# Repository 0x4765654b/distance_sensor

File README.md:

# SaltMon — Water-Softener Salt Level Monitor

SaltMon watches the salt tank of a Culligan Gold Series water softener. A US-100 ultrasonic sensor, mounted under
the tank lid, measures the distance down to the salt. An ESP32-C6 in a wall-mounted box turns that distance into a
salt level. It shows the level on lid LEDs and publishes readings to AWS IoT Core. A SaltMon AWS stack stores the
history, forecasts when the salt will run out, and publishes the results over SNS. There, the ChoreCore household
app picks them up and creates an "Add salt" chore.

**Status:** design phase. The requirements, the carrier schematic and the routed carrier PCB are done. Firmware,
the cloud stack and the tooling are not started yet.

## Repository Layout

```
docs/                     requirements, pin map, integration contract, pick list, datasheets
kicad/lib/                ESP32-C6-DevKitM-1 symbol + socketed footprint (generated)
kicad/DepthSensor/        carrier PCB project (KiCad 10): schematic, board, Gerbers, generator scripts
models/                   ESP32-S3 dev-kit library (not used; kept for reference)
firmware/                 ESP-IDF application                      (planned)
cloud/                    SaltMon-<env> CDK stack + Lambdas        (planned)
tools/                    provision.py, saltmon-config.py          (planned)
```

## Documents

| Document | Contents |
|---|---|
| [docs/requirements.md](docs/requirements.md) | System requirements: design decisions, parts, power, LEDs, sensor, firmware, cloud, mechanics, verification |
| [docs/pinmap.md](docs/pinmap.md) | Kit header pads, carrier connectors, U2 pinout. Source of truth for firmware `board.h` |
| [docs/integration-contract.md](docs/integration-contract.md) | SNS message contract between SaltMon and its consumers (ChoreCore) |
| [docs/pick-list.md](docs/pick-list.md) | Everything to buy or gather for one build (carrier, cables, enclosure) |
| [docs/lid-pick-list.md](docs/lid-pick-list.md) | The lid panel board: parts, LED spacers, mounting hardware, assembly order |

## Hardware

- **Carrier PCB:** 80.5 × 92 mm, 2-layer, all through-hole. The ESP32-C6-DevKitM-1 plugs into female headers.
  The board also carries a TBD62783APG LED driver, the power path (fuse, lid switch loop, Schottky diode), the
  sensor-line filters, and keyed headers for the lid ribbon (J_PANEL) and the sensor ribbon (J_SNS).
- **Lid panel PCB:** 50 × 63 mm, passive, on standoffs behind the lid. It holds 8 flat-top LEDs (salt level,
  network, activity, power) and pads for the panel-mounted on/off slide switch and push-button. A 16-way ribbon
  with an IDC socket at each end connects it 1:1 to the carrier. The same KiCad file carries the 1:1 lid drilling
  template on User.Drawings. What each LED shows is in requirements §5.4.
- **Sensor:** a US-100 in UART mode on a 6-way ribbon, about 1.2 m long.
- **Enclosure:** a gasketed ABS junction box, wall-mounted through its 4 corner holes.

Gerbers for fabrication are in `kicad/DepthSensor/depth_gerber/` (also zipped as `depth_gerber.zip`).

### Regenerating the Schematic and PCB

The schematic, the kit footprint and the PCB are all generated by scripts. Change the script, not the KiCad file,
then regenerate:

```sh
KICAD=/Applications/KiCad/KiCad.app/Contents
KPY=$KICAD/Frameworks/Python.framework/Versions/Current/bin/python3   # KiCad's Python (has pcbnew)
CLI=$KICAD/MacOS/kicad-cli

python3 kicad/lib/gen_devkit.py                    # kit symbol + footprint
python3 kicad/DepthSensor/gen_schematic.py         # schematic (deterministic UUIDs)
$CLI sch erc kicad/DepthSensor/DepthSensor.kicad_sch

$KPY kicad/DepthSensor/gen_pcb.py                  # place, autoroute (Freerouting), pour GND
$KPY kicad/DepthSensor/gen_pcb.py --no-route       # placement only
$CLI pcb drc --schematic-parity kicad/DepthSensor/DepthSensor.kicad_pcb

python3 kicad/LidPanel/gen_schematic.py           # lid panel: same steps
$KPY kicad/LidPanel/gen_pcb.py
$CLI pcb drc --schematic-parity kicad/LidPanel/LidPanel.kicad_pcb
$CLI pcb export pdf --mode-single -l User.Drawings --scale 1 -o lid-template.pdf kicad/LidPanel/LidPanel.kicad_pcb
```

Helpers shared by both boards are in `kicad/lib/schgen.py` (schematic) and `kicad/lib/pcbgen.py` (PCB).

`gen_pcb.py` needs Java 21+ and the Freerouting jar at `kicad/freerouting/freerouting-*.jar`. The jar is not in git;
download it from the [Freerouting releases](https://github.com/freerouting/freerouting/releases). It was tested
with 2.4.1. Close the board in KiCad before regenerating, and re-export the Gerbers afterwards.

## License

[MIT](LICENSE)

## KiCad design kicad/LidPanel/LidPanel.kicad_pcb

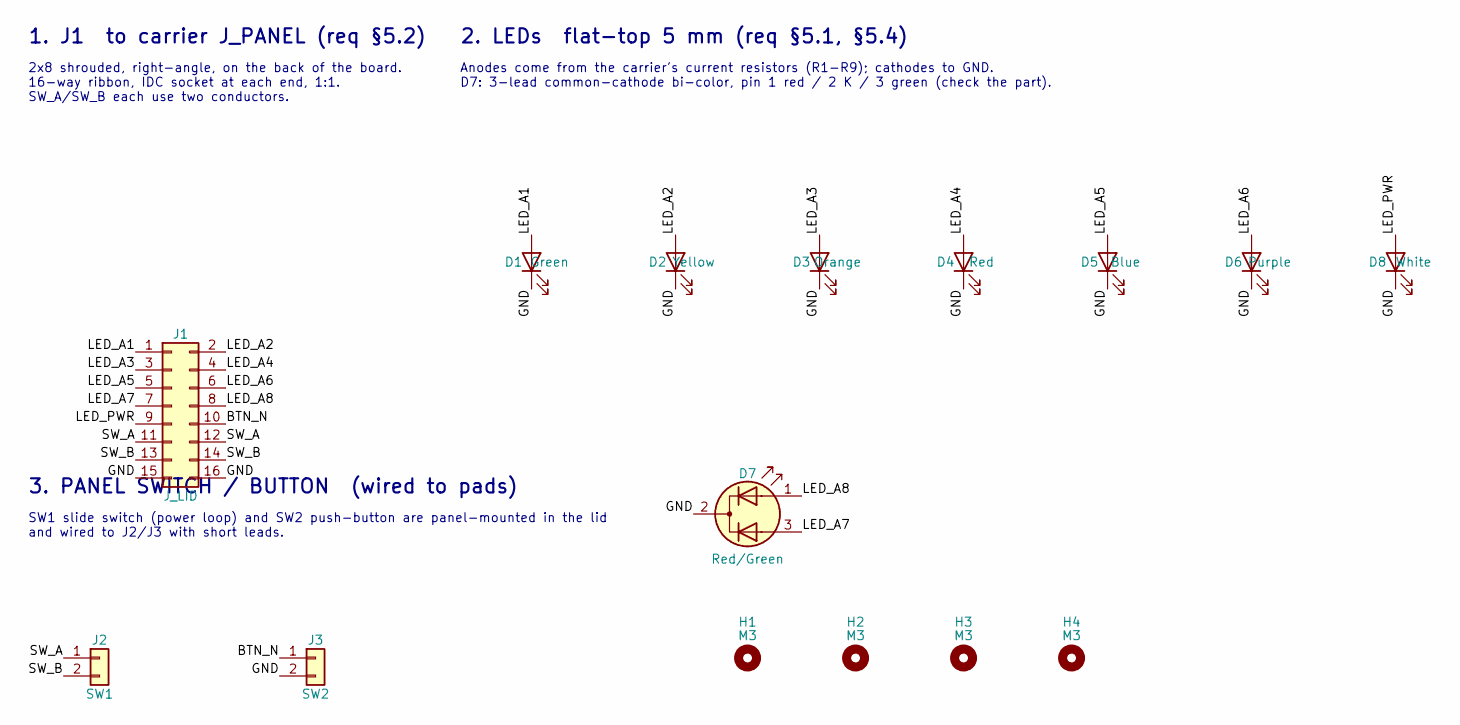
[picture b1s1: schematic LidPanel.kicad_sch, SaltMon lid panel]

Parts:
D1: Green; LED_D5.0mm_FlatTop
D2: Yellow; LED_D5.0mm_FlatTop
D3: Orange; LED_D5.0mm_FlatTop
D4: Red; LED_D5.0mm_FlatTop
D5: Blue; LED_D5.0mm_FlatTop
D6: Purple; LED_D5.0mm_FlatTop
D7: Red/Green; LED_D5.0mm-3
D8: White; LED_D5.0mm_FlatTop
H1, H2, H3, H4: M3; MountingHole_3.2mm_M3
J1: J_LID; IDC-Header_2x08_P2.54mm_Horizontal
J2: SW1; SolderWire-0.5sqmm_1x02_P4.6mm_D0.9mm_OD2.1mm
J3: SW2; SolderWire-0.5sqmm_1x02_P4.6mm_D0.9mm_OD2.1mm

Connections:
/BTN_N: J1.10, J3.1
/GND: D1.1 (K), D2.1 (K), D3.1 (K), D4.1 (K), D5.1 (K), D6.1 (K), D7.2 (K), D8.1 (K), J1.15, J1.16, J3.2
/LED_A1: D1.2 (A), J1.1
/LED_A2: D2.2 (A), J1.2
/LED_A3: D3.2 (A), J1.3
/LED_A4: D4.2 (A), J1.4
/LED_A5: D5.2 (A), J1.5
/LED_A6: D6.2 (A), J1.6
/LED_A7: D7.3 (A2), J1.7
/LED_A8: D7.1 (A1), J1.8
/LED_PWR: D8.2 (A), J1.9
/SW_A: J1.11, J1.12, J2.1
/SW_B: J1.13, J1.14, J2.2

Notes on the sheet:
1. J1 to carrier J_PANEL (req §5.2)
2x8 shrouded, right-angle, on the back of the board. 16-way ribbon, IDC socket at each end, 1:1. SW_A/SW_B each use two conductors.
2. LEDs flat-top 5 mm (req §5.1, §5.4)
Anodes come from the carrier's current resistors (R1-R9); cathodes to GND. D7: 3-lead common-cathode bi-color, pin 1 red / 2 K / 3 green (check the part).
3. PANEL SWITCH / BUTTON (wired to pads)
SW1 slide switch (power loop) and SW2 push-button are panel-mounted in the lid and wired to J2/J3 with short leads.

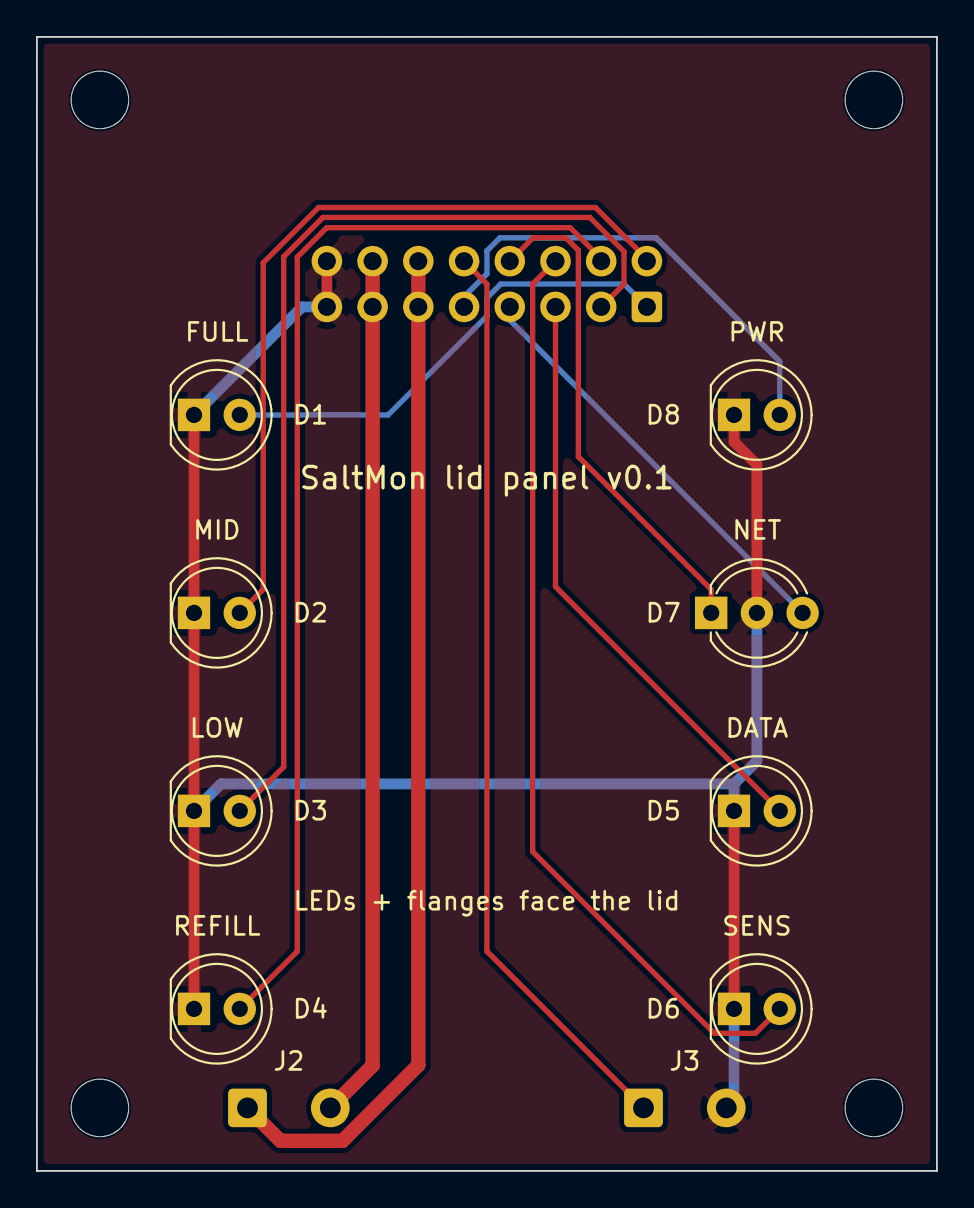
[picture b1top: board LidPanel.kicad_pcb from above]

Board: 2 copper layers, 50.0 x 63.0 mm, 15 parts (1 on the bottom side), 13 nets.

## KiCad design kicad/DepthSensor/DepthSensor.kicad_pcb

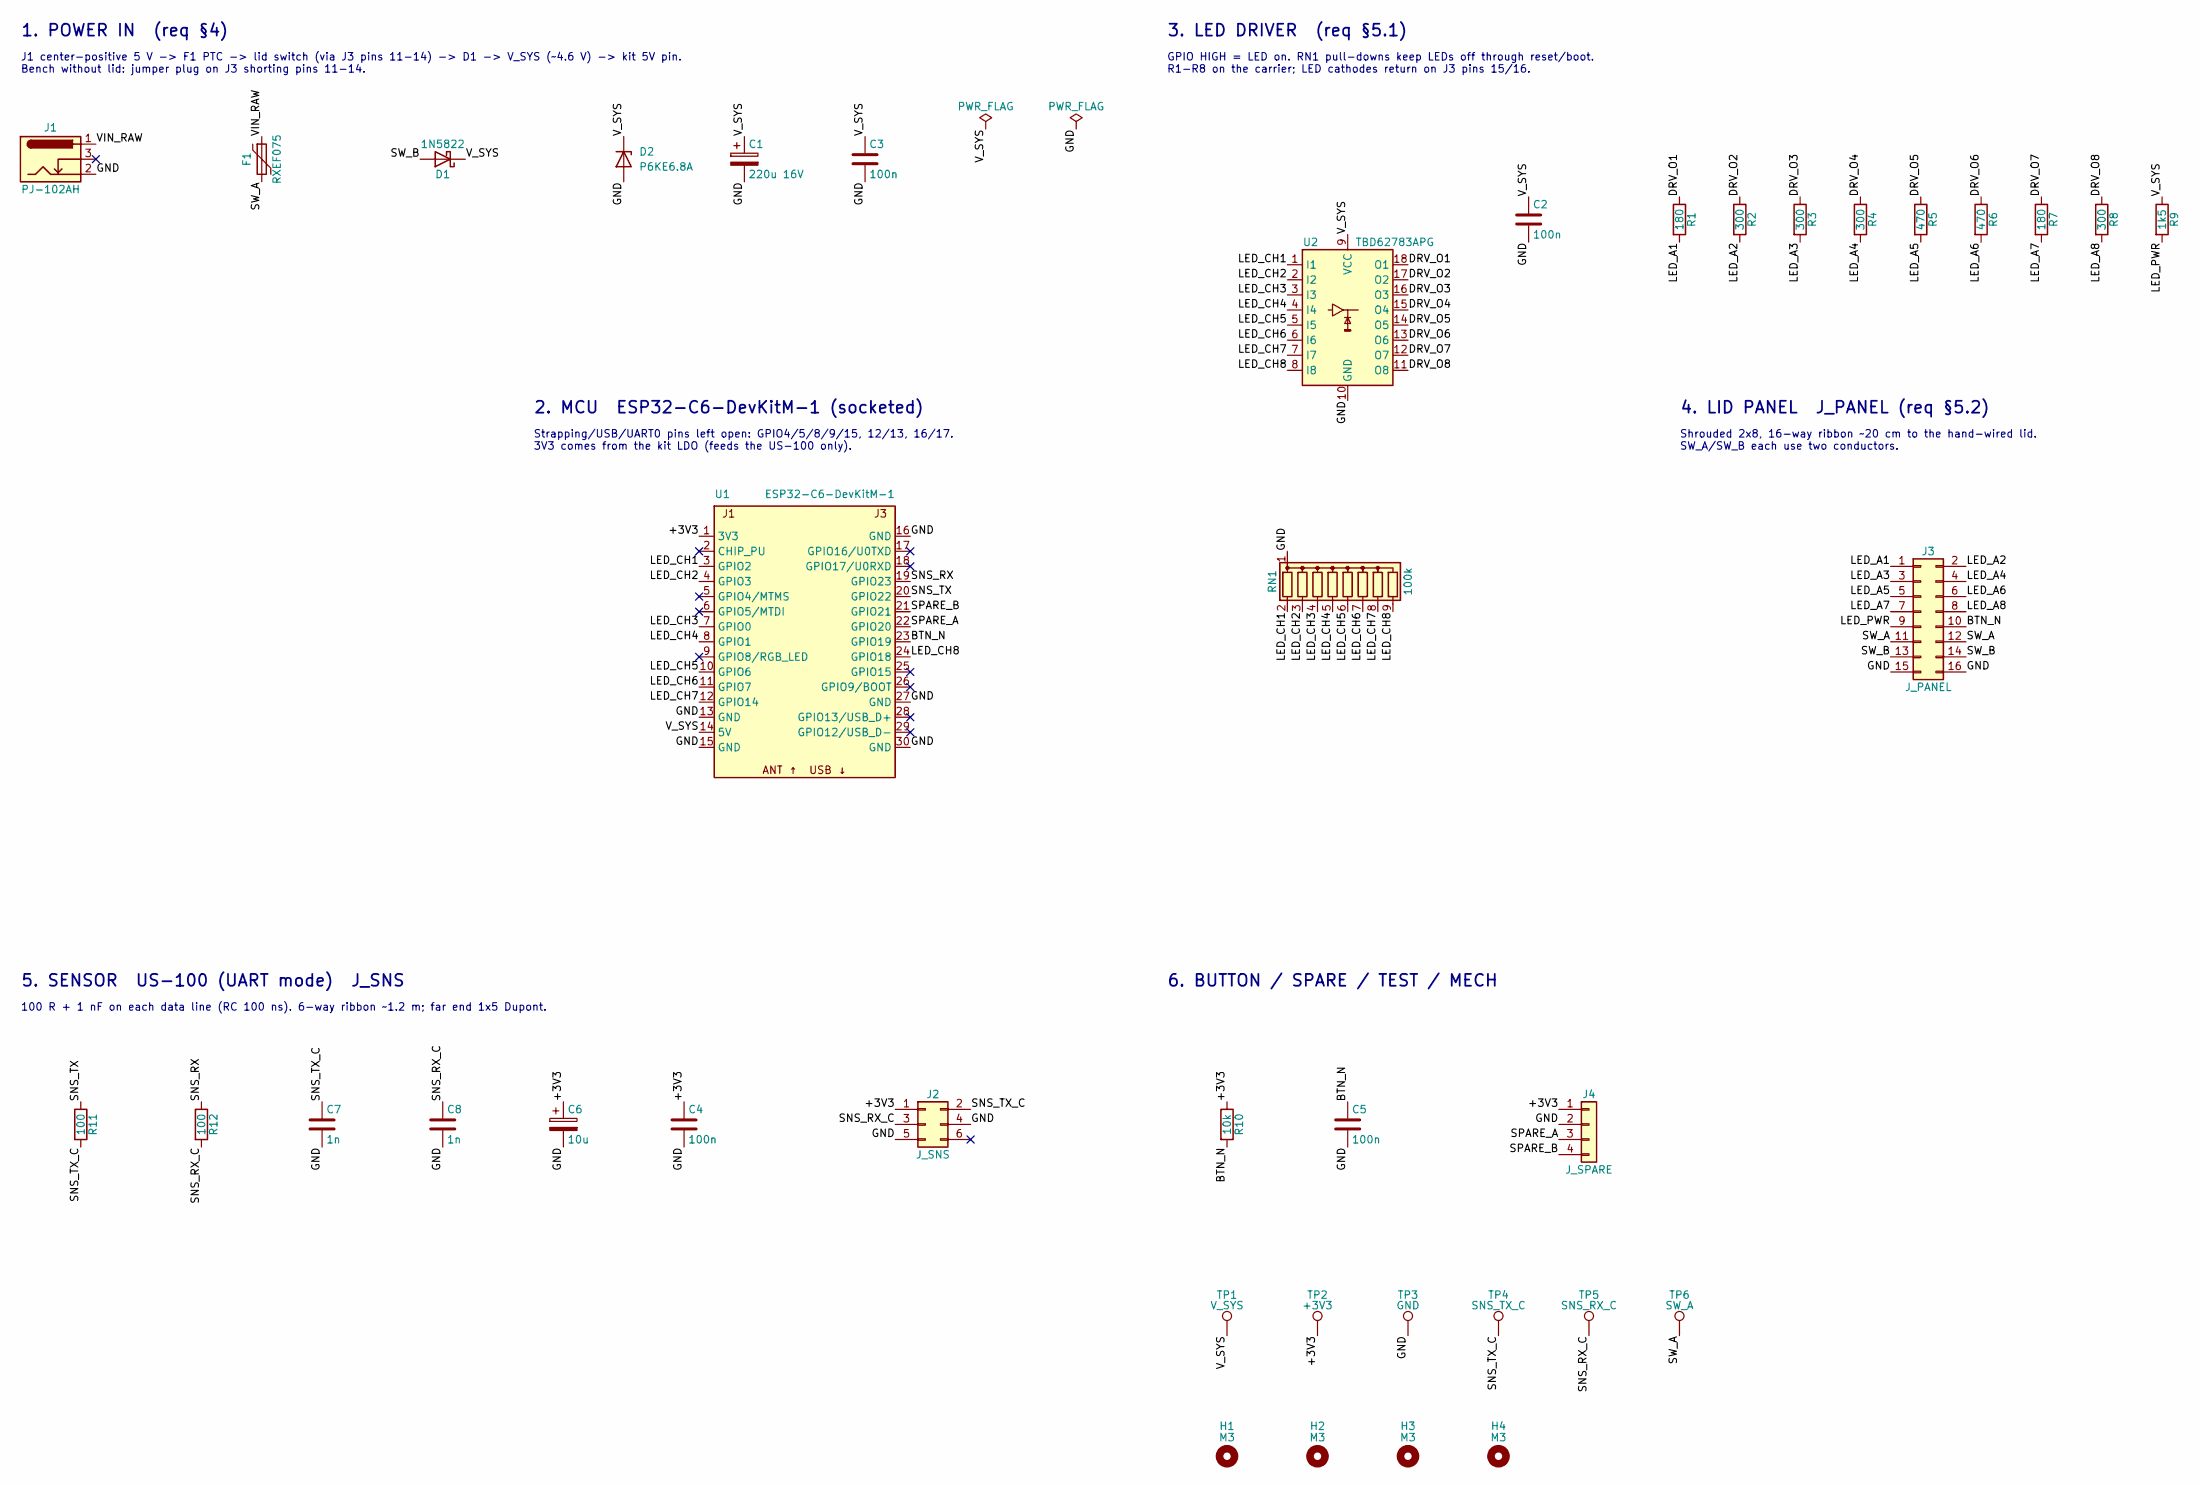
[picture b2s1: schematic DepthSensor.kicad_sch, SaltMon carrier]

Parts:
C1: 220u 16V; CP_Radial_D8.0mm_P3.50mm
C2, C3, C4, C5: 100n; C_Disc_D5.0mm_W2.5mm_P5.00mm
C6: 10u; CP_Radial_D5.0mm_P2.00mm
C7, C8: 1n; C_Disc_D5.0mm_W2.5mm_P5.00mm
D1: 1N5822; D_DO-201AD_P15.24mm_Horizontal
D2: P6KE6.8A; D_DO-15_P10.16mm_Horizontal
F1: RXEF075; Fuse_Bourns_MF-RHT070
H1, H2, H3, H4: M3; MountingHole_3.2mm_M3
J1: PJ-102AH; BarrelJack_CUI_PJ-102AH_Horizontal
J2: J_SNS; IDC-Header_2x03_P2.54mm_Vertical
J3: J_PANEL; IDC-Header_2x08_P2.54mm_Vertical
J4: J_SPARE; PinHeader_1x04_P2.54mm_Vertical
R1, R7: 180; R_Axial_DIN0207_L6.3mm_D2.5mm_P10.16mm_Horizontal
R2, R3, R4, R8: 300; R_Axial_DIN0207_L6.3mm_D2.5mm_P10.16mm_Horizontal
R5, R6: 470; R_Axial_DIN0207_L6.3mm_D2.5mm_P10.16mm_Horizontal
R9: 1k5; R_Axial_DIN0207_L6.3mm_D2.5mm_P10.16mm_Horizontal
R10: 10k; R_Axial_DIN0207_L6.3mm_D2.5mm_P10.16mm_Horizontal
R11, R12: 100; R_Axial_DIN0207_L6.3mm_D2.5mm_P10.16mm_Horizontal
RN1: 100k; R_Array_SIP9
TP1: V_SYS; TestPoint_THTPad_1.5x1.5mm_Drill0.7mm
TP2: +3V3; TestPoint_THTPad_1.5x1.5mm_Drill0.7mm
TP3: GND; TestPoint_THTPad_1.5x1.5mm_Drill0.7mm
TP4: SNS_TX_C; TestPoint_THTPad_1.5x1.5mm_Drill0.7mm
TP5: SNS_RX_C; TestPoint_THTPad_1.5x1.5mm_Drill0.7mm
TP6: SW_A; TestPoint_THTPad_1.5x1.5mm_Drill0.7mm
U1: ESP32-C6-DevKitM-1; ESP32-C6-DevKitM-1_Socketed
U2: TBD62783APG; DIP-18_W7.62mm_Socket

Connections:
/+3V3: C4.1, C6.1, J2.1, J4.1, R10.1, TP2.1, U1.1 (3V3)
/BTN_N: C5.1, J3.10, R10.2, U1.23 (GPIO19)
/DRV_O1: R1.1, U2.18 (O1)
/DRV_O2: R2.1, U2.17 (O2)
/DRV_O3: R3.1, U2.16 (O3)
/DRV_O4: R4.1, U2.15 (O4)
/DRV_O5: R5.1, U2.14 (O5)
/DRV_O6: R6.1, U2.13 (O6)
/DRV_O7: R7.1, U2.12 (O7)
/DRV_O8: R8.1, U2.11 (O8)
/GND: C1.2, C2.2, C3.2, C4.2, C5.2, C6.2, C7.2, C8.2, D2.2 (A), J1.2, J2.4, J2.5, J3.15, J3.16, J4.2, RN1.1 (common), TP3.1, U1.13 (GND), U1.15 (GND), U1.16 (GND), U1.27 (GND), U1.30 (GND), U2.10 (GND)
/LED_A1: J3.1, R1.2
/LED_A2: J3.2, R2.2
/LED_A3: J3.3, R3.2
/LED_A4: J3.4, R4.2
/LED_A5: J3.5, R5.2
/LED_A6: J3.6, R6.2
/LED_A7: J3.7, R7.2
/LED_A8: J3.8, R8.2
/LED_CH1: RN1.2 (R1), U1.3 (GPIO2), U2.1 (I1)
/LED_CH2: RN1.3 (R2), U1.4 (GPIO3), U2.2 (I2)
/LED_CH3: RN1.4 (R3), U1.7 (GPIO0), U2.3 (I3)
/LED_CH4: RN1.5 (R4), U1.8 (GPIO1), U2.4 (I4)
/LED_CH5: RN1.6 (R5), U1.10 (GPIO6), U2.5 (I5)
/LED_CH6: RN1.7 (R6), U1.11 (GPIO7), U2.6 (I6)
/LED_CH7: RN1.8 (R7), U1.12 (GPIO14), U2.7 (I7)
/LED_CH8: RN1.9 (R8), U1.24 (GPIO18), U2.8 (I8)
/LED_PWR: J3.9, R9.2
/SNS_RX: R12.1, U1.19 (GPIO23)
/SNS_RX_C: C8.1, J2.3, R12.2, TP5.1
/SNS_TX: R11.1, U1.20 (GPIO22)
/SNS_TX_C: C7.1, J2.2, R11.2, TP4.1
/SPARE_A: J4.3, U1.22 (GPIO20)
/SPARE_B: J4.4, U1.21 (GPIO21)
/SW_A: F1.2, J3.11, J3.12, TP6.1
/SW_B: D1.2 (A), J3.13, J3.14
/VIN_RAW: F1.1, J1.1
/V_SYS: C1.1, C2.1, C3.1, D1.1 (K), D2.1 (K), R9.1, TP1.1, U1.14 (5V), U2.9 (VCC)

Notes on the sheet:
1. POWER IN (req §4)
J1 center-positive 5 V -> F1 PTC -> lid switch (via J3 pins 11-14) -> D1 -> V_SYS (~4.6 V) -> kit 5V pin. Bench without lid: jumper plug on J3 shorting pins 11-14.
2. MCU ESP32-C6-DevKitM-1 (socketed)
Strapping/USB/UART0 pins left open: GPIO4/5/8/9/15, 12/13, 16/17. 3V3 comes from the kit LDO (feeds the US-100 only).
3. LED DRIVER (req §5.1)
GPIO HIGH = LED on. RN1 pull-downs keep LEDs off through reset/boot. R1-R8 on the carrier; LED cathodes return on J3 pins 15/16.
4. LID PANEL J_PANEL (req §5.2)
Shrouded 2x8, 16-way ribbon ~20 cm to the hand-wired lid. SW_A/SW_B each use two conductors.
5. SENSOR US-100 (UART mode) J_SNS
100 R + 1 nF on each data line (RC 100 ns). 6-way ribbon ~1.2 m; far end 1x5 Dupont.
6. BUTTON / SPARE / TEST / MECH

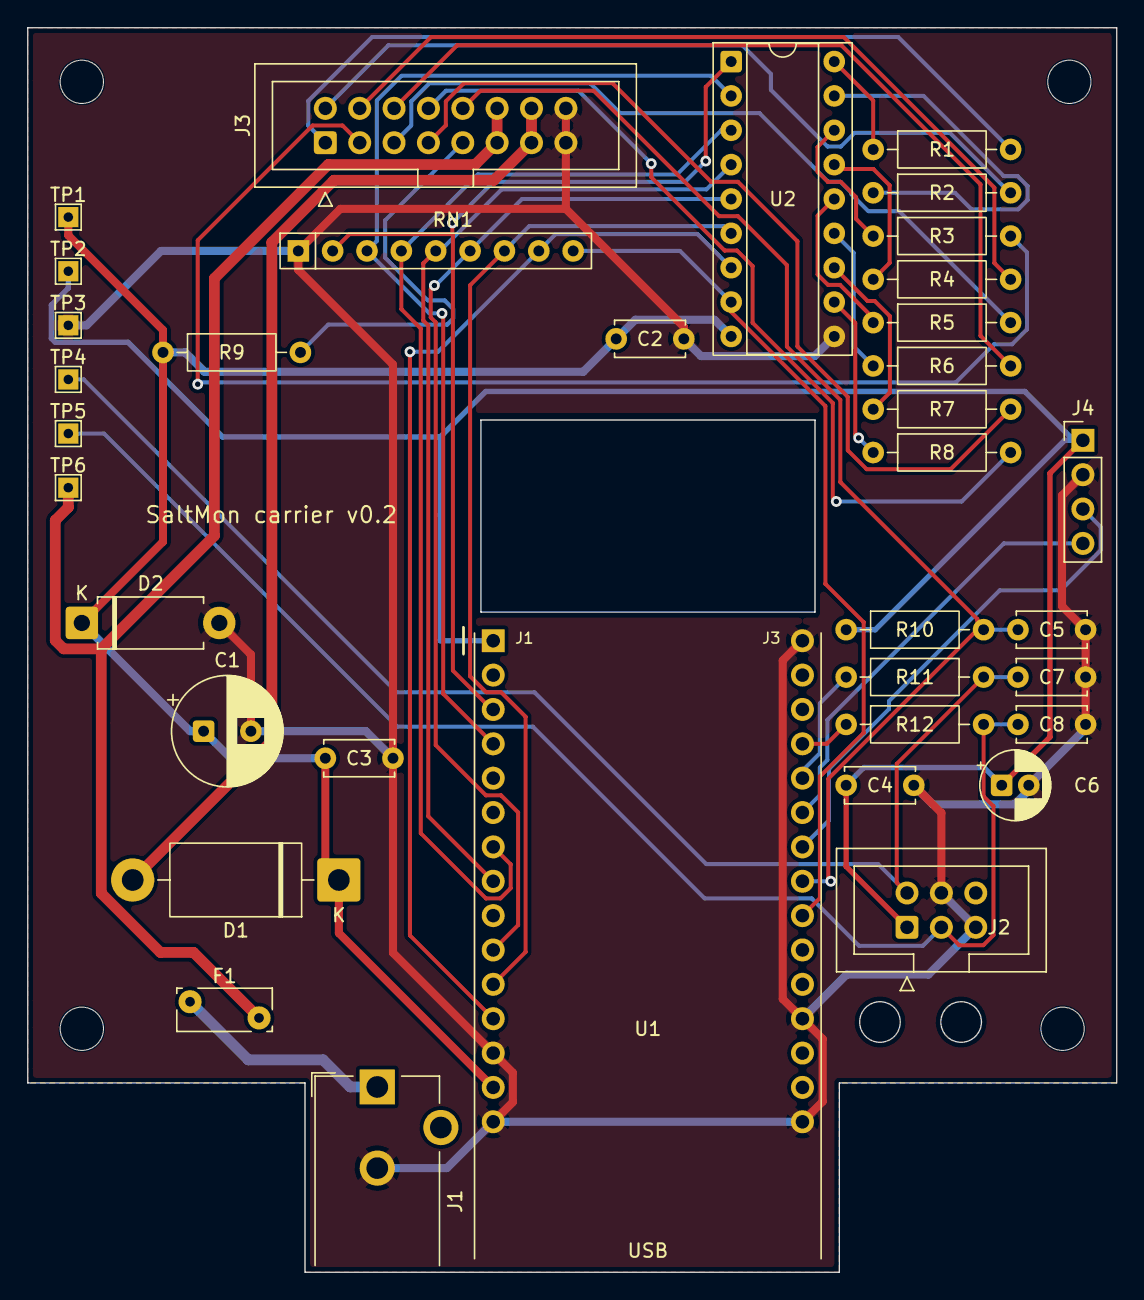
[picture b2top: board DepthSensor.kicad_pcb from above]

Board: 2 copper layers, 80.5 x 92.0 mm, 40 parts (0 on the bottom side), 38 nets.
